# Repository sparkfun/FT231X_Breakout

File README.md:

FT231X Breakout
========================

[  
*FT231X Breakout (BOB-11736)*](https://www.sparkfun.com/products/11736)

This is a simple breakout board for the FTDI FT231X. A **USB to serial UART** interface with full modem control. The board has a micro USB connector, and other support circuitry to get the IC quickly up-and-running.

Repository Contents
-------------------

* **/hardware** - PCB design files (created with Eagle 6.1.0)
* **/Production Files** - Test bed files and production panel files

License Information
-------------------

All contents of this repository are released under [Creative Commons Share-alike 3.0](http://creativecommons.org/licenses/by-sa/3.0/).

Author
------

Jim Lindblom, [SparkFun Electronics](https://www.sparkfun.com)

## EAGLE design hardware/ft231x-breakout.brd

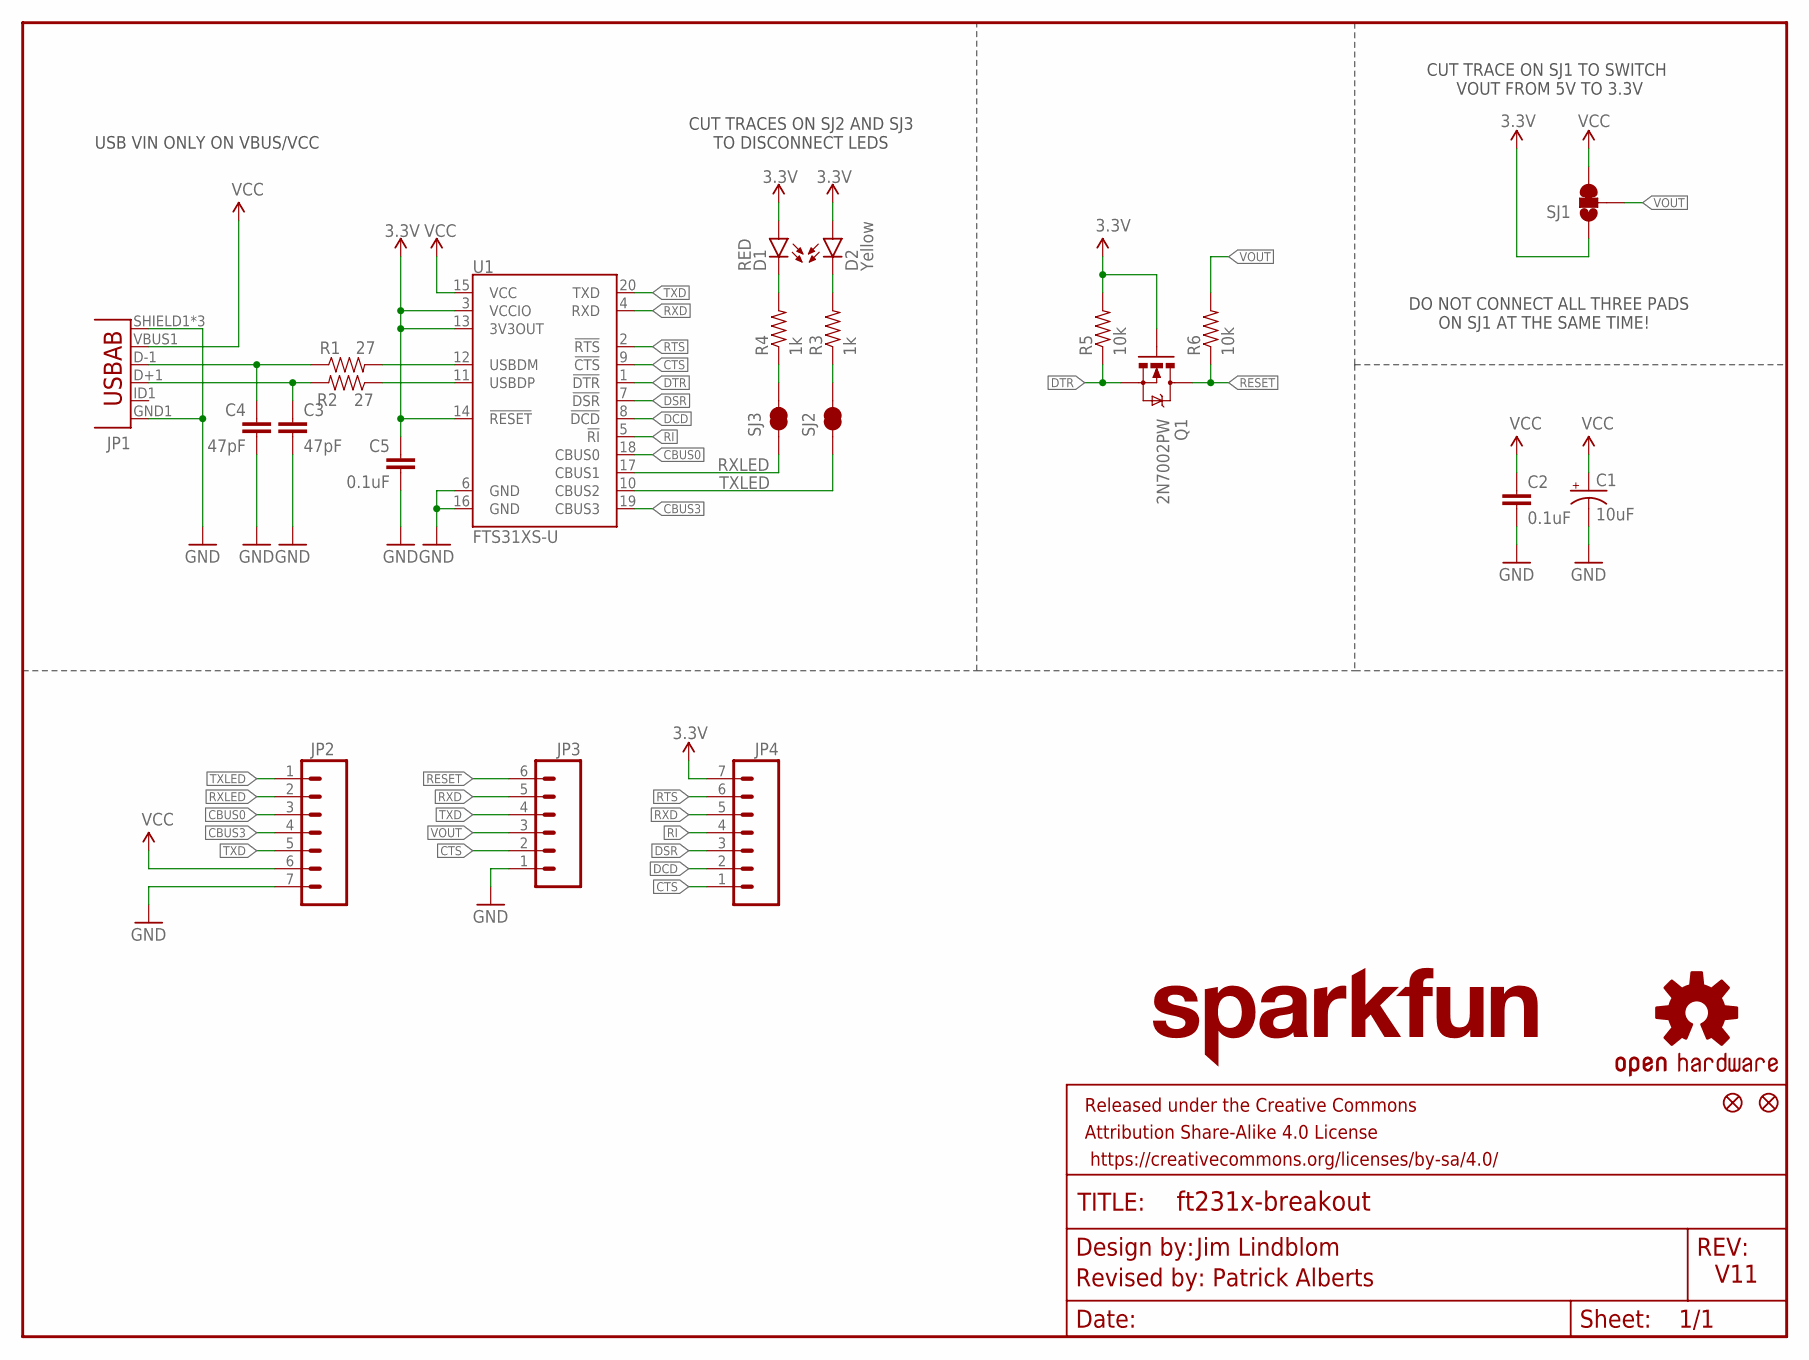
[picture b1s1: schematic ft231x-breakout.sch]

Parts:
C1: 10uF; EIA3216
C2, C5: 0.1uF; 0603-CAP
C3, C4: 47pF; 0603-CAP
D1: RED; LED-0603
D2: Yellow; LED-0603
FRAME1: FRAME-LETTER; CREATIVE_COMMONS
JP1: USB-ABCONN-11794; USB-AB-MICRO-SMD_V03
JP2, JP4: M07NO_SILK; 1X07_NO_SILK
JP3: M06NO_SILK_FEMALE_PTH; 1X06_NO_SILK
JP5, JP6: FIDUCIAL1X2; FIDUCIAL-1X2
LOGO1: SFE_LOGO_NAME.1_INCH; SFE_LOGO_NAME_.1
Q1: 2N7002PW; SOT323
R1, R2: 27; 0603-RES
R3, R4: 1k; 0603-RES@1
R5, R6: 10k; 0603-RES@1
SJ1: SOLDERJUMPER_2WAYS; SJ_3
SJ2: TXLED; SJ_2S-TRACE
SJ3: RXLED; PAD-JUMPER-2-NC_BY_TRACE_YES_SILK
U1: FTS31XS-U; SSOP20_L
U$1: OSHW-LOGOS; OSHW-LOGO-S

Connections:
3.3V: C5.1, D1.A, D2.A, JP4.7, Q1.1 (G), R5.2, SJ1.1, U1.3 (VCCIO), U1.13 (3V3OUT), U1.14 (!RESET)
CBUS0: JP2.3, U1.18 (CBUS0)
CBUS3: JP2.4, U1.19 (CBUS3)
CTS: JP3.2, JP4.1, U1.9 (!CTS)
DCD: JP4.2, U1.8 (!DCD)
DSR: JP4.3, U1.7 (!DSR)
DTR: Q1.2 (S), R5.1, U1.1 (!DTR)
GND: C1.C (-), C2.2, C3.2, C4.2, C5.2, JP1.GND1 (GND), JP1.SHIELD1 (SHIELD), JP1.SHIELD2 (SHIELD), JP1.SHIELD3 (SHIELD), JP2.7, JP3.1, U1.6 (GND), U1.16 (GND)
unnamed: R1.2, U1.12 (USBDM)
unnamed: R2.1, U1.11 (USBDP)
unnamed: C3.1, JP1.D+1 (D+), R2.2
unnamed: C4.1, JP1.D-1 (D-), R1.1
unnamed: D2.C, R3.2
unnamed: D1.C, R4.2
unnamed: R3.1, SJ2.2
unnamed: R4.1, SJ3.2
RESET: JP3.6, Q1.3 (D), R6.1
RI: JP4.4, U1.5 (!RI)
RTS: JP4.6, U1.2 (!RTS)
RXD: JP3.5, JP4.5, U1.4 (RXD)
RXLED: JP2.2, SJ3.1, U1.17 (CBUS1)
TXD: JP2.5, JP3.4, U1.20 (TXD)
TXLED: JP2.1, SJ2.1, U1.10 (CBUS2)
VCC: C1.A (+), C2.1, JP1.VBUS1 (VBUS), JP2.6, SJ1.3, U1.15 (VCC)
VOUT: JP3.3, R6.2, SJ1.2

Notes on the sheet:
V11
Jim Lindblom
Revised by: Patrick Alberts
USB VIN ONLY ON VBUS/VCC
CUT TRACES ON SJ2 AND SJ3 TO DISCONNECT LEDS
CUT TRACE ON SJ1 TO SWITCH VOUT FROM 5V TO 3.3V
DO NOT CONNECT ALL THREE PADS ON SJ1 AT THE SAME TIME!

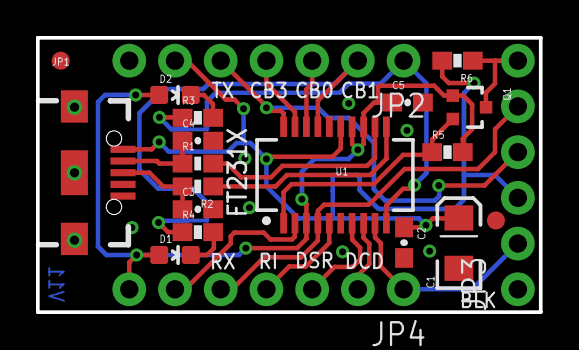
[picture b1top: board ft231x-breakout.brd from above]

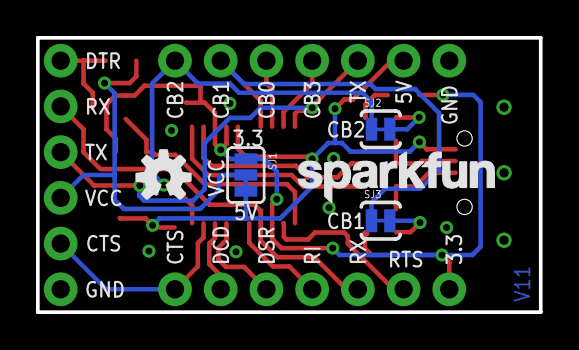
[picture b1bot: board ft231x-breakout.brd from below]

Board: 2 copper layers, 27.9 x 15.2 mm, 27 parts (5 on the bottom side), 25 nets.

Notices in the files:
parts and their libraries:
SparkFun-Aesthetics: Licensing: CC v3.0 Share-Alike You are welcome to use this library for commercial purposes.
SparkFun-Retired: Licensing:Creative Commons ShareAlike 4.0 International - https://creativecommons.org/licenses/by-sa/4.0
SparkFun-Aesthetics: Released under the Creative Commons
